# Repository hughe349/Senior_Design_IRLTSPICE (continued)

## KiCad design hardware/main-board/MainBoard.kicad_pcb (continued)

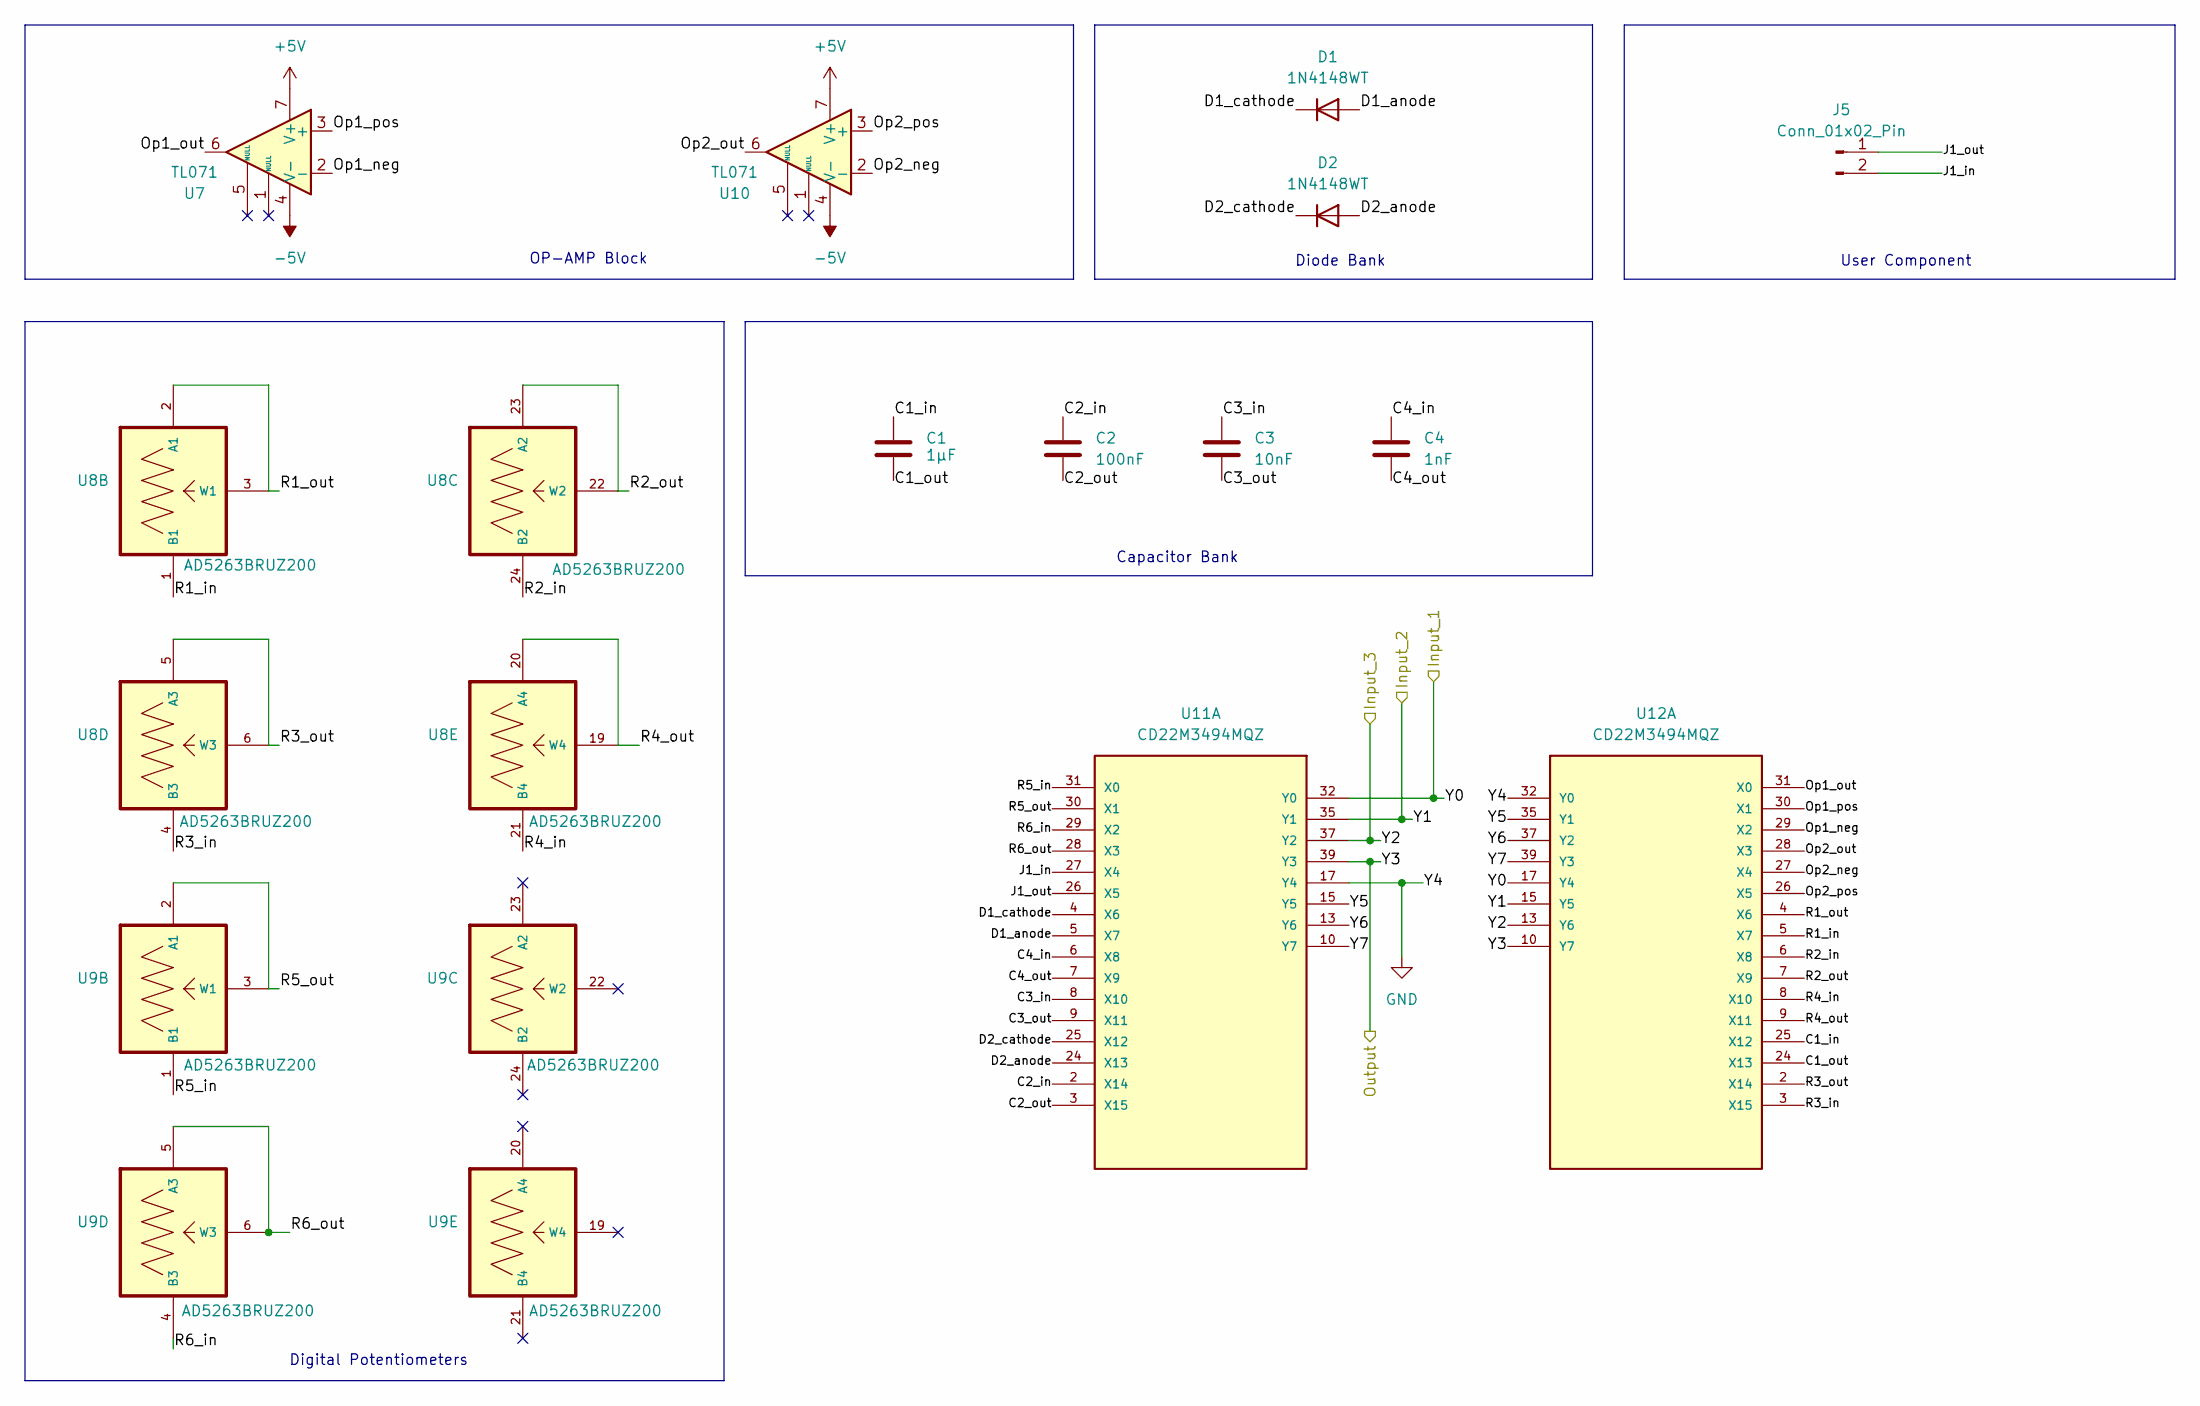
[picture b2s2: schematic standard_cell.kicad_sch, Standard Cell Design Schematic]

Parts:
C1: 1µF; C_0603_1608Metric_Pad1.08x0.95mm_HandSolder
C2: 100nF; C_0603_1608Metric_Pad1.08x0.95mm_HandSolder
C3: 10nF; C_0603_1608Metric_Pad1.08x0.95mm_HandSolder
C4: 1nF; C_0603_1608Metric_Pad1.08x0.95mm_HandSolder
D1, D2: 1N4148WT; D_SOD-123
J5: Conn_01x02_Pin; PinSocket_1x02_P2.54mm_Vertical
U7, U10: TL071; SOIC-8_3.9x4.9mm_P1.27mm
U8, U9: AD5263BRUZ200; SOP65P640X120-24N
U11, U12: CD22M3494MQZ; PLCC44_16P66X16P66_INR-M; PARTREV September 2011

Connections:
+5V: U7.7 (V+), U10.7 (V+); also elsewhere on the board
-5V: U7.4 (V-), U10.4 (V-); also elsewhere on the board
/Cell_0_Out: U11.39 (Y3), U12.10 (Y7); also elsewhere on the board
/STD/C1_in: C1.1, U12.25 (X12)
/STD/C1_out: C1.2, U12.24 (X13)
/STD/C2_in: C2.1, U11.2 (X14)
/STD/C2_out: C2.2, U11.3 (X15)
/STD/C3_in: C3.1, U11.8 (X10)
/STD/C3_out: C3.2, U11.9 (X11)
/STD/C4_in: C4.1, U11.6 (X8)
/STD/C4_out: C4.2, U11.7 (X9)
/STD/D1_anode: D1.2 (A), U11.5 (X7)
/STD/D1_cathode: D1.1 (K), U11.4 (X6)
/STD/D2_anode: D2.2 (A), U11.24 (X13)
/STD/D2_cathode: D2.1 (K), U11.25 (X12)
/STD/J1_in: J5.2, U11.27 (X4)
/STD/J1_out: J5.1, U11.26 (X5)
/STD/Op1_neg: U7.2 (-), U12.29 (X2)
/STD/Op1_out: U7.6, U12.31 (X0)
/STD/Op1_pos: U7.3 (+), U12.30 (X1)
/STD/Op2_neg: U10.2 (-), U12.27 (X4)
/STD/Op2_out: U10.6, U12.28 (X3)
/STD/Op2_pos: U10.3 (+), U12.26 (X5)
/STD/R1_in: U8.1 (B1), U12.5 (X7)
/STD/R1_out: U8.2 (A1), U8.3 (W1), U12.4 (X6)
/STD/R2_in: U8.24 (B2), U12.6 (X8)
/STD/R2_out: U8.22 (W2), U8.23 (A2), U12.7 (X9)
/STD/R3_in: U8.4 (B3), U12.3 (X15)
/STD/R3_out: U8.5 (A3), U8.6 (W3), U12.2 (X14)
/STD/R4_in: U8.21 (B4), U12.8 (X10)
/STD/R4_out: U8.19 (W4), U8.20 (A4), U12.9 (X11)
/STD/R5_in: U9.1 (B1), U11.31 (X0)
/STD/R5_out: U9.2 (A1), U9.3 (W1), U11.30 (X1)
/STD/R6_in: U9.4 (B3), U11.29 (X2)
/STD/R6_out: U9.5 (A3), U9.6 (W3), U11.28 (X3)
/STD/Y5: U11.15 (Y5), U12.35 (Y1)
/STD/Y6: U11.13 (Y6), U12.37 (Y2)
/STD/Y7: U11.10 (Y7), U12.39 (Y3)
/STD_Y0: U11.32 (Y0), U12.17 (Y4); also elsewhere on the board
/STD_Y1: U11.35 (Y1), U12.15 (Y5); also elsewhere on the board
/STD_Y2: U11.37 (Y2), U12.13 (Y6); also elsewhere on the board
GND: U11.17 (Y4), U12.32 (Y0); also elsewhere on the board

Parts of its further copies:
C5, C9, C13: 1µF; C_0603_1608Metric_Pad1.08x0.95mm_HandSolder
C6, C10, C14: 100nF; C_0603_1608Metric_Pad1.08x0.95mm_HandSolder
C7, C11, C15: 10nF; C_0603_1608Metric_Pad1.08x0.95mm_HandSolder
C8, C12, C16: 1nF; C_0603_1608Metric_Pad1.08x0.95mm_HandSolder
D3, D4, D5, D6, D7, D8: 1N4148WT; D_SOD-123
J6, J7, J8: Conn_01x02_Pin; PinSocket_1x02_P2.54mm_Vertical
U13, U16, U19, U22, U25, U28: TL071; SOIC-8_3.9x4.9mm_P1.27mm

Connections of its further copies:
+5V: U13.7 (V+), U16.7 (V+), U19.7 (V+), U22.7 (V+), U25.7 (V+), U28.7 (V+); also elsewhere on the board
-5V: U13.4 (V-), U16.4 (V-), U19.4 (V-), U22.4 (V-), U25.4 (V-), U28.4 (V-); also elsewhere on the board
/STD1/C1_in: C5.1; also elsewhere on the board
/STD1/C1_out: C5.2; also elsewhere on the board
/STD1/C2_in: C6.1; also elsewhere on the board
/STD1/C2_out: C6.2; also elsewhere on the board
/STD1/C3_in: C7.1; also elsewhere on the board
/STD1/C3_out: C7.2; also elsewhere on the board
/STD1/C4_in: C8.1; also elsewhere on the board
/STD1/C4_out: C8.2; also elsewhere on the board
/STD1/D1_anode: D3.2 (A); also elsewhere on the board
/STD1/D1_cathode: D3.1 (K); also elsewhere on the board
/STD1/D2_anode: D4.2 (A); also elsewhere on the board
/STD1/D2_cathode: D4.1 (K); also elsewhere on the board
/STD1/J1_in: J6.2; also elsewhere on the board
/STD1/J1_out: J6.1; also elsewhere on the board
/STD1/Op1_neg: U13.2 (-); also elsewhere on the board
/STD1/Op1_out: U13.6; also elsewhere on the board
/STD1/Op1_pos: U13.3 (+); also elsewhere on the board
/STD1/Op2_neg: U16.2 (-); also elsewhere on the board
/STD1/Op2_out: U16.6; also elsewhere on the board
/STD1/Op2_pos: U16.3 (+); also elsewhere on the board
/STD2/C1_in: C9.1; also elsewhere on the board
/STD2/C1_out: C9.2; also elsewhere on the board
/STD2/C2_in: C10.1; also elsewhere on the board
/STD2/C2_out: C10.2; also elsewhere on the board
/STD2/C3_in: C11.1; also elsewhere on the board
/STD2/C3_out: C11.2; also elsewhere on the board
/STD2/C4_in: C12.1; also elsewhere on the board
/STD2/C4_out: C12.2; also elsewhere on the board
/STD2/D1_anode: D5.2 (A); also elsewhere on the board
/STD2/D1_cathode: D5.1 (K); also elsewhere on the board
/STD2/D2_anode: D6.2 (A); also elsewhere on the board
/STD2/D2_cathode: D6.1 (K); also elsewhere on the board
/STD2/J1_in: J7.2; also elsewhere on the board
/STD2/J1_out: J7.1; also elsewhere on the board
/STD2/Op1_neg: U19.2 (-); also elsewhere on the board
/STD2/Op1_out: U19.6; also elsewhere on the board
/STD2/Op1_pos: U19.3 (+); also elsewhere on the board
/STD2/Op2_neg: U22.2 (-); also elsewhere on the board
/STD2/Op2_out: U22.6; also elsewhere on the board
/STD2/Op2_pos: U22.3 (+); also elsewhere on the board
/STD3/C1_in: C13.1; also elsewhere on the board
/STD3/C1_out: C13.2; also elsewhere on the board
/STD3/C2_in: C14.1; also elsewhere on the board
/STD3/C2_out: C14.2; also elsewhere on the board
/STD3/C3_in: C15.1; also elsewhere on the board
/STD3/C3_out: C15.2; also elsewhere on the board
/STD3/C4_in: C16.1; also elsewhere on the board
/STD3/C4_out: C16.2; also elsewhere on the board
/STD3/D1_anode: D7.2 (A); also elsewhere on the board
/STD3/D1_cathode: D7.1 (K); also elsewhere on the board
/STD3/D2_anode: D8.2 (A); also elsewhere on the board
/STD3/D2_cathode: D8.1 (K); also elsewhere on the board
/STD3/J1_in: J8.2; also elsewhere on the board
/STD3/J1_out: J8.1; also elsewhere on the board
/STD3/Op1_neg: U25.2 (-); also elsewhere on the board
/STD3/Op1_out: U25.6; also elsewhere on the board
/STD3/Op1_pos: U25.3 (+); also elsewhere on the board
/STD3/Op2_neg: U28.2 (-); also elsewhere on the board
/STD3/Op2_out: U28.6; also elsewhere on the board
/STD3/Op2_pos: U28.3 (+); also elsewhere on the board

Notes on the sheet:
Diode Bank
Digital Potentiometers
User Component
OP-AMP Block
Capacitor Bank

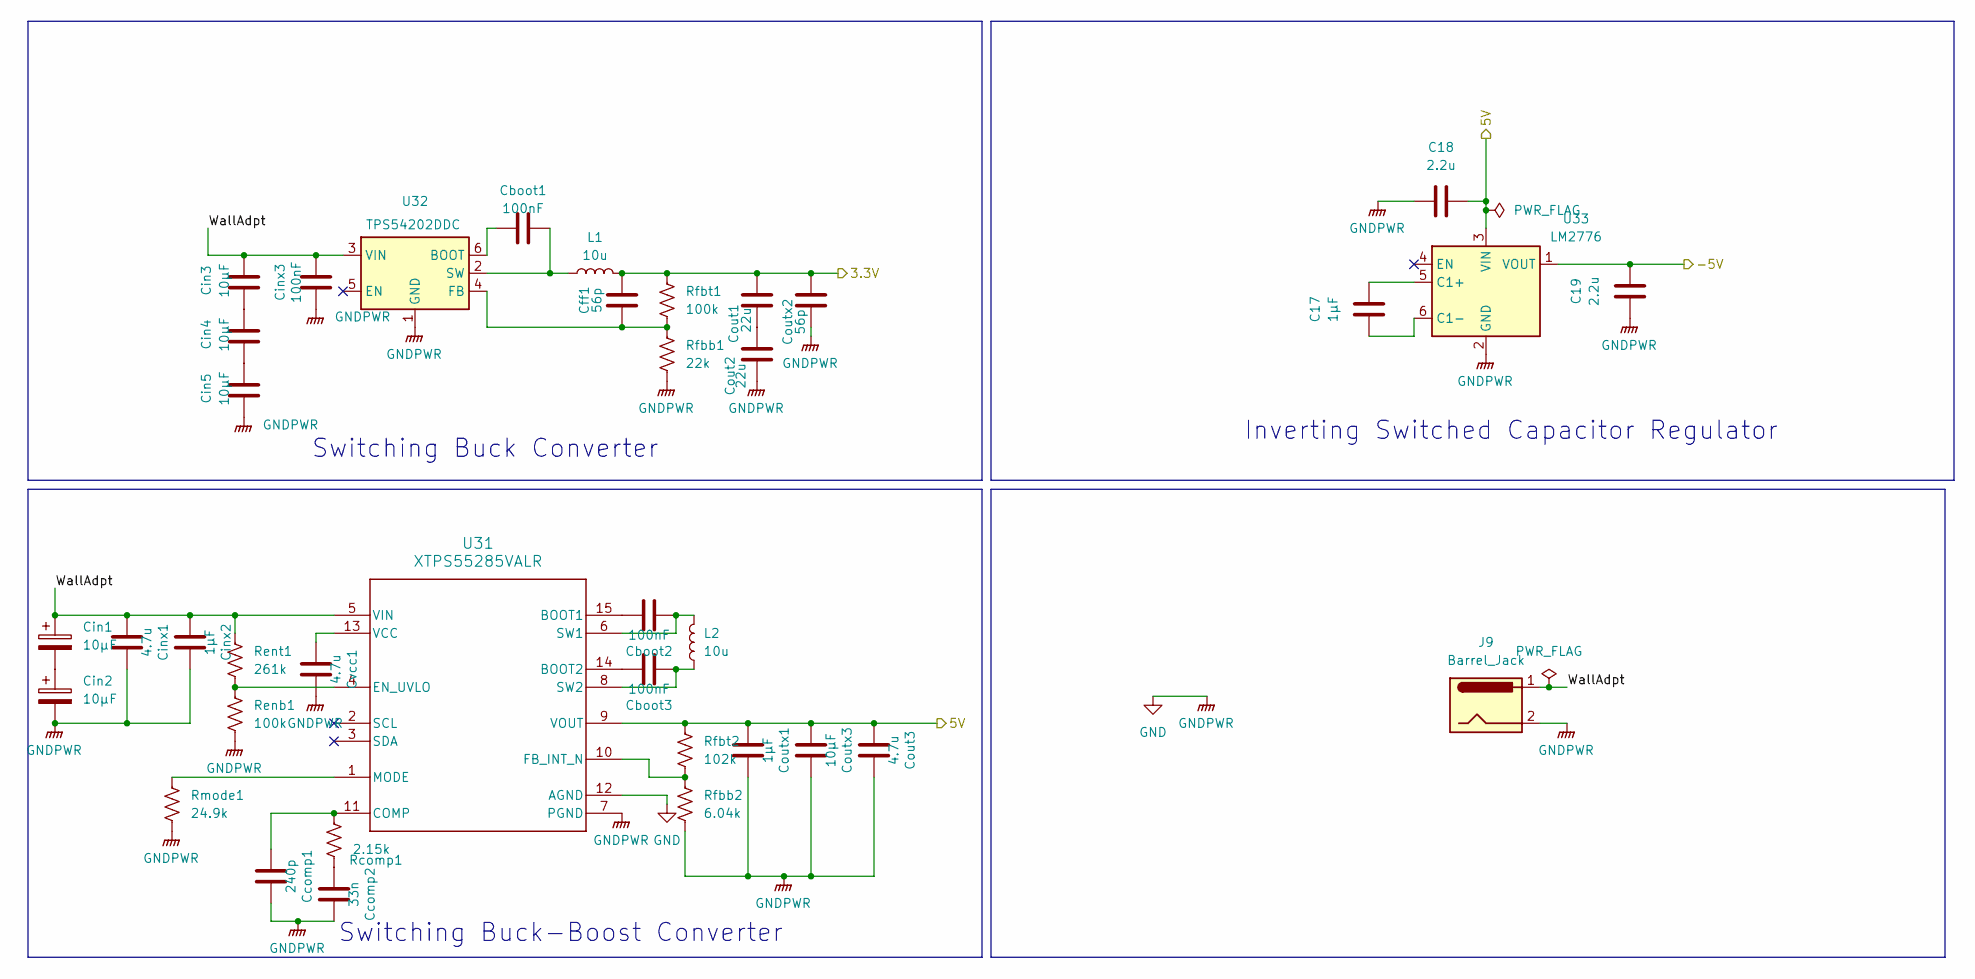
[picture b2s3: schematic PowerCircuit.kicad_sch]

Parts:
C17: 1µF; C_0603_1608Metric_Pad1.08x0.95mm_HandSolder
C18, C19: 2.2u; C_0603_1608Metric_Pad1.08x0.95mm_HandSolder
Cboot1, Cboot2, Cboot3: 100nF; C_0402_1005Metric_Pad0.74x0.62mm_HandSolder
Ccomp1: 240p; C_0402_1005Metric_Pad0.74x0.62mm_HandSolder
Ccomp2: 33n; C_0402_1005Metric_Pad0.74x0.62mm_HandSolder
Cff1: 56p; C_0201_0603Metric_Pad0.64x0.40mm_HandSolder
Cin1, Cin2: 10µF; CAP_EEFK_C_PAN
Cin3, Cin4, Cin5: 10µF; C_1210_3225Metric_Pad1.33x2.70mm_HandSolder
Cinx1: 4.7u; C_1210_3225Metric_Pad1.33x2.70mm_HandSolder
Cinx2: 1µF; C_0402_1005Metric_Pad0.74x0.62mm_HandSolder
Cinx3: 100nF; C_0402_1005Metric_Pad0.74x0.62mm_HandSolder
Cout1, Cout2: 22u; C_0805_2012Metric_Pad1.18x1.45mm_HandSolder
Cout3: 4.7u; C_1206_3216Metric_Pad1.33x1.80mm_HandSolder
Coutx1: 1µF; C_0201_0603Metric_Pad0.64x0.40mm_HandSolder
Coutx2: 56p; R_0402_1005Metric_Pad0.72x0.64mm_HandSolder
Coutx3: 10µF; C_1210_3225Metric_Pad1.33x2.70mm_HandSolder
Cvcc1: 4.7u; C_0201_0603Metric_Pad0.64x0.40mm_HandSolder
J9: Barrel_Jack; BarrelJack_CUI_PJ-063AH_Horizontal
L1: 10u; L_Bourns-SRU1028_10.0x10.0mm
L2: 10u; L_Bourns_SDR0604
Rcomp1: 2.15k; R_0402_1005Metric_Pad0.72x0.64mm_HandSolder
Renb1: 100k; R_0402_1005Metric_Pad0.72x0.64mm_HandSolder
Rent1: 261k; R_0402_1005Metric_Pad0.72x0.64mm_HandSolder
Rfbb1: 22k; R_0201_0603Metric_Pad0.64x0.40mm_HandSolder
Rfbb2: 6.04k; R_0402_1005Metric_Pad0.72x0.64mm_HandSolder
Rfbt1: 100k; R_0402_1005Metric_Pad0.72x0.64mm_HandSolder
Rfbt2: 102k; R_0402_1005Metric_Pad0.72x0.64mm_HandSolder
Rmode1: 24.9k; R_0402_1005Metric_Pad0.72x0.64mm_HandSolder
U31: XTPS55285VALR; TPS55285
U32: TPS54202DDC; SOT-23-6
U33: LM2776; SOT-23-6

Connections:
/Power Supply/3.3V: Cff1.2, Cout1.2, Coutx2.2, L1.2, Rfbt1.1; also elsewhere on the board
/Power Supply/5V: C18.2, Cout3.1, Coutx1.1, Coutx3.1, Rfbt2.1, U31.9 (VOUT), U33.3 (VIN); also elsewhere on the board
/Power Supply/-5V: C19.2, U33.1 (VOUT); also elsewhere on the board
/Power Supply/WallAdpt: Cin1.1, Cin3.2, Cinx1.1, Cinx2.1, J9.1, Rent1.1, U31.5 (VIN), U32.3 (VIN)
GND: C18.1, C19.1, Ccomp1.2, Ccomp2.2, Cin1.2, Cin2.1, Cin3.1, Cin4.2, Cinx1.2, Cinx2.2, Cout1.1, Cout2.2, Cout3.2, Coutx1.2, Coutx3.2, Cvcc1.2, J9.2, Renb1.2, Rfbb1.2, Rfbb2.2, Rmode1.2, U31.7 (PGND), U31.12 (AGND), U32.1 (GND), U33.2 (GND); also elsewhere on the board
unnamed: Ccomp2.1, Rcomp1.2
unnamed: Cin4.1, Cin5.2
unnamed: Cboot2.2, U31.15 (BOOT1)
unnamed: Cboot3.2, U31.14 (BOOT2)
unnamed: Ccomp1.1, Rcomp1.1, U31.11 (COMP)
unnamed: Renb1.1, Rent1.2, U31.4 (EN_UVLO)
unnamed: Rfbb2.1, Rfbt2.2, U31.10 (FB_INT_N)
unnamed: Rmode1.1, U31.1 (MODE)
unnamed: Cboot2.1, L2.2, U31.6 (SW1)
unnamed: Cboot3.1, L2.1, U31.8 (SW2)
unnamed: Cvcc1.1, U31.13 (VCC)
unnamed: Cboot1.1, U32.6 (BOOT)
unnamed: Cff1.1, Rfbb1.1, Rfbt1.2, U32.4 (FB)
unnamed: Cboot1.2, L1.1, U32.2 (SW)
unnamed: C17.2, U33.5 (C1+)
unnamed: C17.1, U33.6 (C1-)

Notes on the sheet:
Switching Buck Converter
Inverting Switched Capacitor Regulator
Switching Buck-Boost Converter
